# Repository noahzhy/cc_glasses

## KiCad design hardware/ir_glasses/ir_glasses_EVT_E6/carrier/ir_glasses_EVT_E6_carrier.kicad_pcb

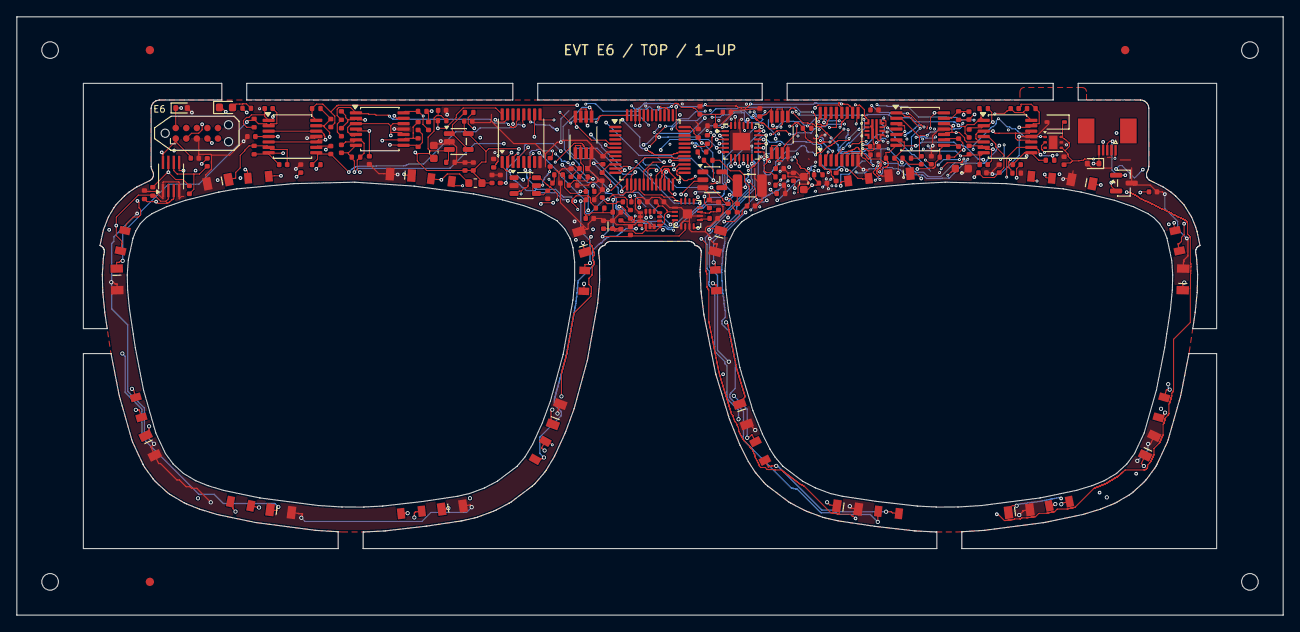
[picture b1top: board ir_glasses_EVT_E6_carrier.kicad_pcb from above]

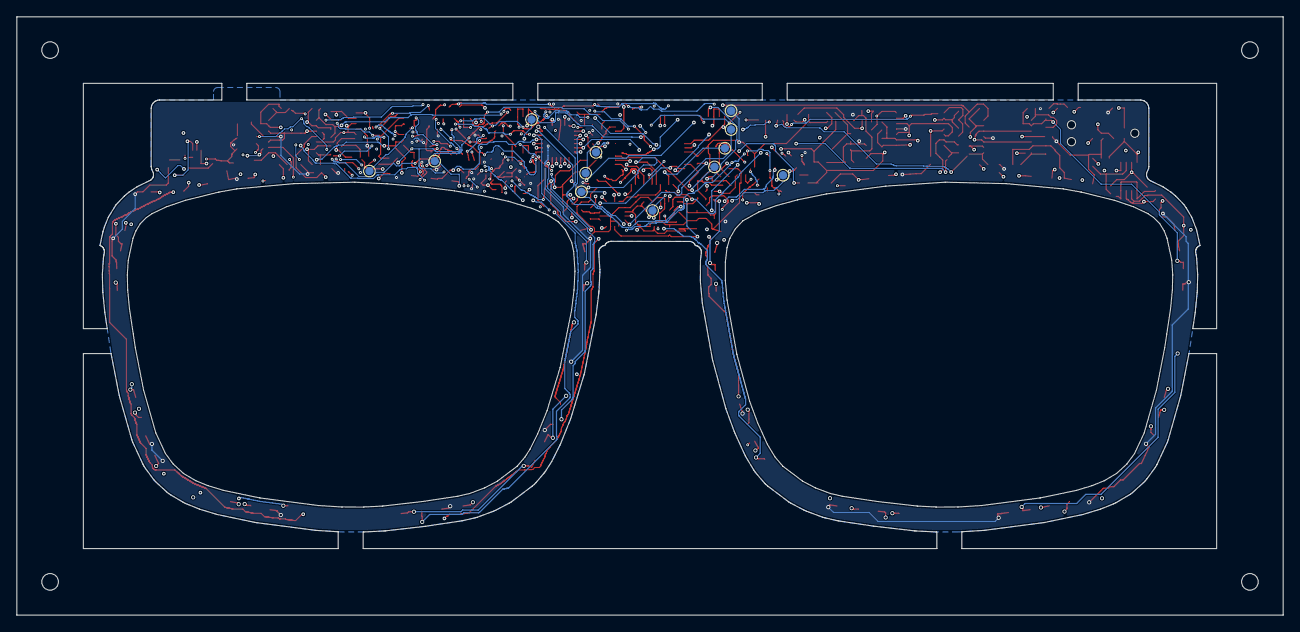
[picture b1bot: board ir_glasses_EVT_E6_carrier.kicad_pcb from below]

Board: 4 copper layers, 152.3 x 72.0 mm, 187 parts (12 on the bottom side), 110 nets.

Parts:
C1, C18, C19, C20, C21, C22, C23, C24, C37, C39, C40, C41, C43, C46, C47: 1u; 0402
C2, C3, C4, C5, C6, C7, C8, C9, C10, C11, C12, C13, C14, C15, C16, C17, C31, C32, C35, C36, C42, C44, C45, C48, C49: 100n; 0402
C25, C26, C27: 10u; 0603
C28: 47u 16V X5R; 1210
C29, C30: 330p C0G; 0402
C33, C34: 1n; 0402
C38: 22n X7R; 0402
CF1, CF2, CF3, CF4, CF5, CF6, CF7, CF8, CF9, CF10, CF11, CF12, CF13, CF14, CF15, CF16: 22p C0G; 0402
D1, D2, D3, D4, D5, D6, D7, D8, D9, D10, D11, D12, D13, D14, D15, D16: IR11-21C/TR8; 1206
D17: PESD5V0S1BA,115; SOD-323
D18, D19: PESD3V3U1UB,115; SOD-523
D20: GREEN / STATUS; 0603
FB1: 600R@100MHz 500mA; 0603
FID1, FID2, FID3: Fiducial_1mm_Mask2mm
H1, H2, H3, H4: MountingHole_2mm
J1: 0.5K-AS-5PWB-RW; GUOCONN_0.5K-AS-5PWB-RW
J2: TC2050-IDC-NL / ARM2010; TC2050
PD1, PD2, PD3, PD4, PD5, PD6, PD7, PD8, PD9, PD10, PD11, PD12, PD13, PD14, PD15, PD16: PD15-21B/TR8; 1206
R1: 2.67k; 0402
R2, R3, R4, R10, R16, R19, R26, R27, R28: 10k; 0402
R5, R15: 100k; 0402
R6, R7, R17: 4.7k; 0402
R8, R9: 22; 0402
R11, R12, R14, R25: 100; 0402
R13: 47; 0402
R18: 200; 0402
R20: 6.2k; 0402
R21, R23: 10k 0.1%; 0402
R22, R24: 20k 0.1%; 0402
R29: 110k; 0402
RF1, RF2, RF3, RF4, RF5, RF6, RF7, RF8, RF9, RF10, RF11, RF12, RF13, RF14, RF15, RF16: 100k; 0402
TP1, TP10: 3V3; 1mm
TP2: GND; 1mm
TP3: UART_TX; 1mm
TP4: UART_RX; 1mm
TP5: BOOT_TX_PA9; 1mm
TP6: BOOT_RX_PA10; 1mm
TP7: SWCLK_BOOT0; 1mm
TP8: NRST; 1mm
TP9: VREF_1V65; 1mm
TP11: IMU_INT; 1mm
TP12: 3V3_A; 1mm
U1: TLC59283RGER; VQFN-24
U2, U3, U4, U5: TLV9064IPWR; TSSOP-14
U6: TLV9061IDBVR; SOT-23-5
U7, U8: TMUX1308PWR; TSSOP-16
U9: STM32C031C6T6; LQFP-48
U10: LSM6DS3TR-C; LGA-14
U11: PESD3V3L2BT,215; SOT-23
U12: SN74LVC1G123DCTR; SSOP-8
U13: SN74LVC1G04DBVR; SOT-23-5
U14: TPS259470ARPWR; VQFN-10-HR
U15: AD7386BCPZ-RL7; LFCSP-16_3x3mm_P0.5mm_EP1.1x1.1mm
U16, U17: TLV9062IDGKR; VSSOP-8_3x3mm_P0.65mm
U18: TPS2553DRVR; TPS2553_DRV0006
U19: TPS3702CX33DDCR; TPS3702_DDC0006

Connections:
3V3: C2.1, C10.1, C12.1, C13.1, C14.1, C16.1, C17.1, C18.1, C19.1, C20.1, C24.1, C25.1, C26.1, C28.1, C35.1, C36.1, C40.1, D1.1, D2.1, D3.1, D4.1, D5.1, D6.1, D7.1, D8.1, D9.1, D10.1, D11.1, D12.1, D13.1, D14.1, D15.1, D16.1, FB1.1, J2.1, R4.1, R6.1, R7.1, R10.1, R15.1, R17.1, R26.2, R27.2, TP1.1, TP10.1, U1.21, U9.6, U10.5, U10.8, U10.12, U12.2, U12.8, U13.5, U14.6, U15.2
3V3_A: C3.1, C4.1, C5.1, C6.1, C7.1, C8.1, C9.1, C11.1, C15.1, C21.1, C22.1, C23.1, C27.1, C39.1, C44.1, C45.1, C46.1, C47.1, FB1.2, R2.1, TP12.1, U2.4, U3.4, U4.4, U5.4, U6.5, U7.16, U8.16, U9.5, U15.4, U16.8, U17.8
ADC_A: C29.1, R11.2, U15.8
ADC_B: C30.1, R12.2, U15.6
ADC_CS_N: R26.1, U9.11, U15.12
ADC_MISO: R25.2, U9.17
ADC_MOSI: U9.18, U15.15
ADC_REFCAP: C42.1, U15.9
ADC_REF_2V5: C43.1, U15.11
ADC_REGCAP: C41.1, U15.3
ADC_SCLK: U9.16, U15.16
ADC_SDO_RAW: R25.1, U15.13
BOOT_RX_PA10: TP6.1, U9.32
BOOT_TX_PA9: TP5.1, U9.29
BUF_A: R21.1, U16.1, U16.2
BUF_B: R23.1, U17.1, U17.2
DRIVE_A: R11.1, U16.6, U16.7
DRIVE_B: R12.1, U17.6, U17.7
GND: C1.2, C2.2, C3.2, C4.2, C5.2, C6.2, C7.2, C8.2, C9.2, C10.2, C11.2, C12.2, C13.2, C14.2, C15.2, C16.2, C17.2, C18.2, C19.2, C20.2, C21.2, C22.2, C23.2, C24.2, C25.2, C26.2, C27.2, C28.2, C29.2, C30.2, C31.2, C32.2, C35.2, C36.2, C37.2, C38.2, C39.2, C40.2, C41.2, C42.2, C43.2, C44.2, C45.2, C46.2, C47.2, C48.2, C49.2, D17.2, D18.2, D19.2, J1.2, J2.3, PD1.1, PD2.1, PD3.1, PD4.1, PD5.1, PD6.1, PD7.1, PD8.1, PD9.1, PD10.1, PD11.1, PD12.1, PD13.1, PD14.1, PD15.1, PD16.1, R1.2, R3.2, R5.2, R16.2, R19.2, R20.2, R22.2, R24.2, R29.2, TP2.1, U1.22, U1.25, U2.11, U3.11, U4.11, U5.11, U6.2, U7.8, U8.8, U9.7, U10.1, U10.2, U10.3, U10.6, U10.7, U11.3, U12.1, U12.4, U13.3, U14.2, U14.8, U15.1, U15.5, U15.7, U15.10, U15.17, U16.4, U17.4, U18.5, U18.7, U19.2
HOST_RX: J1.4, R9.1, U11.2
HOST_TX: J1.3, R8.2, U11.1
I2C_SCL: R6.2, U9.45, U10.13
I2C_SDA: R7.2, U9.46, U10.14
ILIM_SET: R20.1, U14.9
IMU_INT: TP11.1, U9.21, U10.4
INPUT_ILIM: R29.1, U18.2
INPUT_OK: R28.2, U14.1, U19.6
INRUSH_RC: C38.1, U14.7
IREF: R1.1, U1.20
LED_BLANK: R10.2, U1.18, U13.4
LED_ENABLE: R16.1, U9.27, U12.3
LED_K1: D1.2, U1.2
LED_K2: D2.2, U1.3
LED_K3: D3.2, U1.4
LED_K4: D4.2, U1.5
LED_K5: D5.2, U1.6
LED_K6: D6.2, U1.7
LED_K7: D7.2, U1.8
LED_K8: D8.2, U1.9
LED_K9: D9.2, U1.10
LED_K10: D10.2, U1.11
LED_K11: D11.2, U1.12
LED_K12: D12.2, U1.13
LED_K13: D13.2, U1.14
LED_K14: D14.2, U1.15
LED_K15: D15.2, U1.16
LED_K16: D16.2, U1.17
LED_LAT: U1.1, U9.20
LED_SCLK: U1.24, U9.22
LED_SIN: U1.23, U9.23
LED_WINDOW: U12.5, U13.2
MUX_A: U7.3, U16.3
MUX_A0: U7.11, U9.15
MUX_A1: U7.10, U9.12
MUX_A2: U7.9, U9.48
MUX_B: U8.3, U17.3
MUX_B0: U8.11, U9.30
MUX_B1: U8.10, U9.38
MUX_B2: U8.9, U9.26
MUX_EN_N: R27.1, U7.6, U8.6, U9.19
NRST: C32.1, D19.1, J2.10, R4.2, R14.2, TP8.1, U9.10
NRST_EXT: D18.1, J1.5, R14.1
OV_SENSE: R18.2, R19.1, U19.3
PD_IN1: CF1.2, PD1.2, RF1.2, U2.2
PD_IN2: CF2.2, PD2.2, RF2.2, U2.6
PD_IN3: CF3.2, PD3.2, RF3.2, U2.9
PD_IN4: CF4.2, PD4.2, RF4.2, U2.13
PD_IN5: CF5.2, PD5.2, RF5.2, U3.2
PD_IN6: CF6.2, PD6.2, RF6.2, U3.6
PD_IN7: CF7.2, PD7.2, RF7.2, U3.9
PD_IN8: CF8.2, PD8.2, RF8.2, U3.13
PD_IN9: CF9.2, PD9.2, RF9.2, U4.2
PD_IN10: CF10.2, PD10.2, RF10.2, U4.6
PD_IN11: CF11.2, PD11.2, RF11.2, U4.9
PD_IN12: CF12.2, PD12.2, RF12.2, U4.13
PD_IN13: CF13.2, PD13.2, RF13.2, U5.2
PD_IN14: CF14.2, PD14.2, RF14.2, U5.6
PD_IN15: CF15.2, PD15.2, RF15.2, U5.9
PD_IN16: CF16.2, PD16.2, RF16.2, U5.13
PULSE_C: C33.1, C34.1, U12.6
PULSE_RC: C33.2, C34.2, R15.2, U12.7
SCALE_A: R21.2, R22.1, U16.5
SCALE_B: R23.2, R24.1, U17.5
STATUS_A: D20.2, R17.2
STATUS_LED_N: D20.1, U9.28
SWCLK_BOOT0: J2.4, R5.1, TP7.1, U9.36
SWDIO: J2.2, U9.35
TIA1: CF1.1, RF1.1, U2.1, U7.13
TIA2: CF2.1, RF2.1, U2.7, U8.13
TIA3: CF3.1, RF3.1, U2.8, U7.14
TIA4: CF4.1, RF4.1, U2.14, U8.14
TIA5: CF5.1, RF5.1, U3.1, U7.15
TIA6: CF6.1, RF6.1, U3.7, U8.15
TIA7: CF7.1, RF7.1, U3.8, U7.12
TIA8: CF8.1, RF8.1, U3.14, U8.12
TIA9: CF9.1, RF9.1, U4.1, U7.1
TIA10: CF10.1, RF10.1, U4.7, U8.1
TIA11: CF11.1, RF11.1, U4.8, U7.5
TIA12: CF12.1, RF12.1, U4.14, U8.5
TIA13: CF13.1, RF13.1, U5.1, U7.2
TIA14: CF14.1, RF14.1, U5.7, U8.2
TIA15: CF15.1, RF15.1, U5.8, U7.4
TIA16: CF16.1, RF16.1, U5.14, U8.4
UART_RX: R9.2, TP4.1, U9.14
UART_TX: R8.1, TP3.1, U9.13
VIN_3V3: C37.1, C49.1, R18.1, R28.1, U14.5, U18.1, U19.4, U19.5
VIN_HOST: C48.1, D17.1, J1.1, U18.4, U18.6
VREF_1V65: C31.1, R13.2, TP9.1, U2.3, U2.5, U2.10, U2.12, U3.3, U3.5, U3.10, U3.12, U4.3, U4.5, U4.10, U4.12, U5.3, U5.5, U5.10, U5.12
VREF_BUF: R13.1, U6.1, U6.4
VREF_DIV: C1.1, R2.2, R3.1, U6.3
